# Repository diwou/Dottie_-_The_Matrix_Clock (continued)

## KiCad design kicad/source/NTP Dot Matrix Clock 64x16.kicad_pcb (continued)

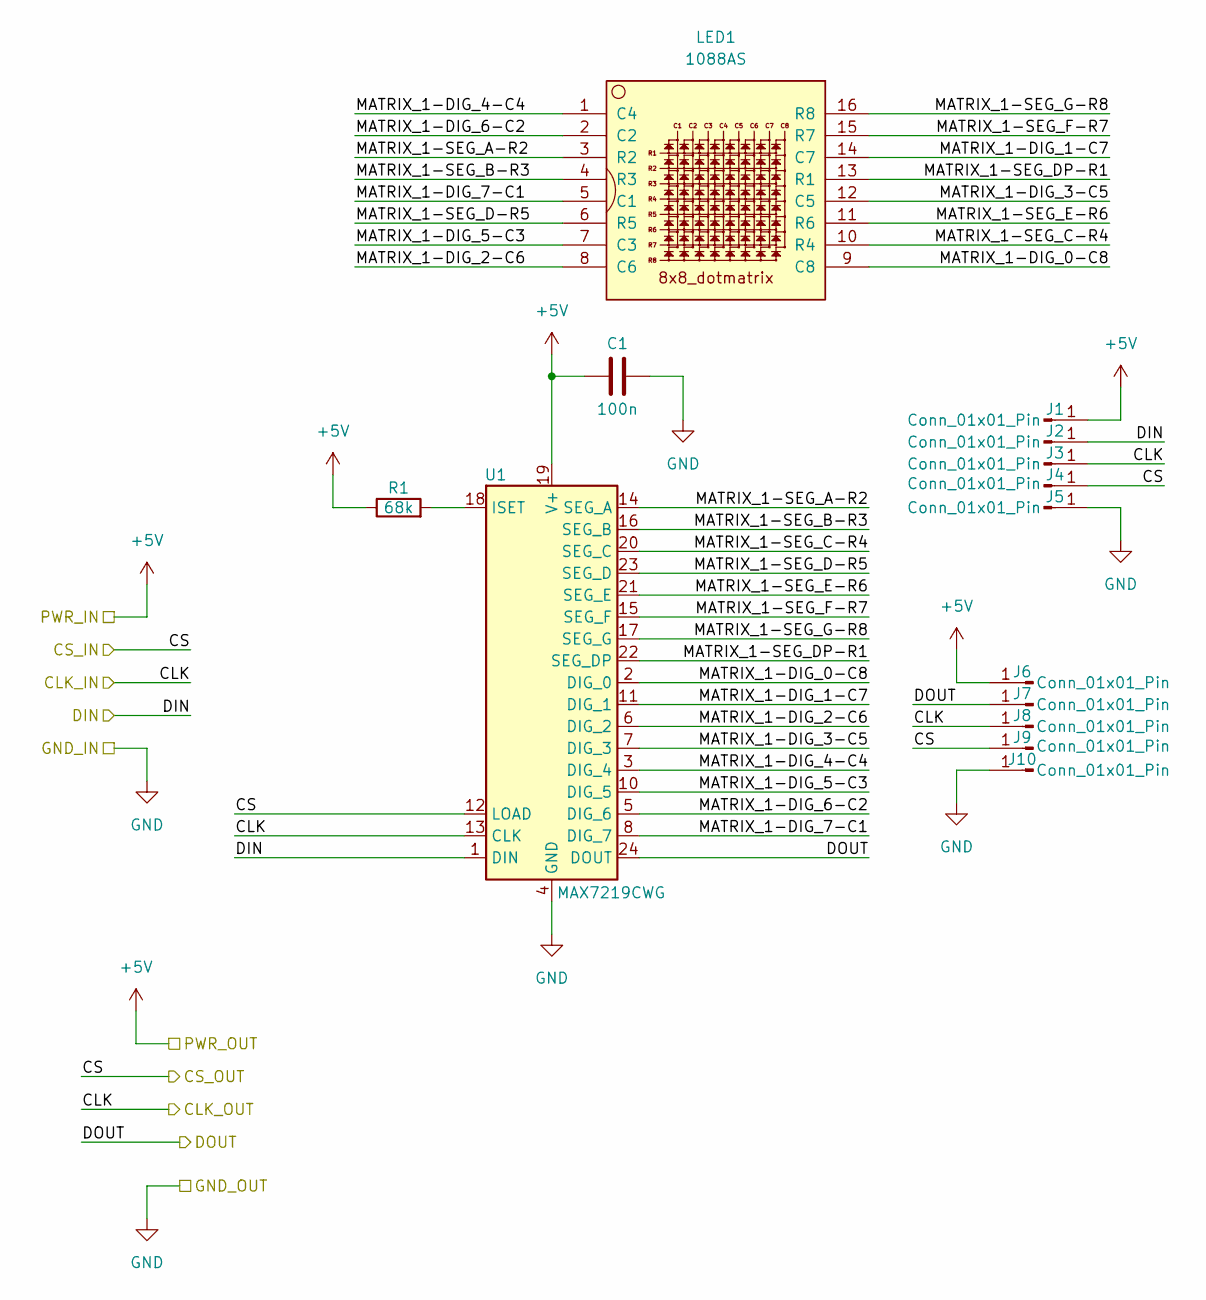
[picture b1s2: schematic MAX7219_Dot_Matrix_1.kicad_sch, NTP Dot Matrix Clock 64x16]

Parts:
C1: 100n; C_0805_2012Metric_Pad1.18x1.45mm_HandSolder
J1, J2, J3, J4, J5, J6, J7, J8, J9, J10: Conn_01x01_Pin; TestPoint_Pad_1.5x1.5mm
LED1: 1088AS; LED_1088_Pin_Header
R1: 68k; R_0805_2012Metric_Pad1.20x1.40mm_HandSolder
U1: MAX7219CWG; SOIC-24W_7.5x15.4mm_P1.27mm

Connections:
+5V: C1.1, J1.1 (Pin_1_1), J6.1 (Pin_1_1), R1.1, U1.19 (V+); also elsewhere on the board
/MAX7219 Dot Matrix 1/DOUT: J7.1 (Pin_1_1), U1.24 (DOUT); also elsewhere on the board
/MAX7219 Dot Matrix 1/MATRIX_1-DIG_0-C8: LED1.9 (C8), U1.2 (DIG_0)
/MAX7219 Dot Matrix 1/MATRIX_1-DIG_1-C7: LED1.14 (C7), U1.11 (DIG_1)
/MAX7219 Dot Matrix 1/MATRIX_1-DIG_2-C6: LED1.8 (C6), U1.6 (DIG_2)
/MAX7219 Dot Matrix 1/MATRIX_1-DIG_3-C5: LED1.12 (C5), U1.7 (DIG_3)
/MAX7219 Dot Matrix 1/MATRIX_1-DIG_4-C4: LED1.1 (C4), U1.3 (DIG_4)
/MAX7219 Dot Matrix 1/MATRIX_1-DIG_5-C3: LED1.7 (C3), U1.10 (DIG_5)
/MAX7219 Dot Matrix 1/MATRIX_1-DIG_6-C2: LED1.2 (C2), U1.5 (DIG_6)
/MAX7219 Dot Matrix 1/MATRIX_1-DIG_7-C1: LED1.5 (C1), U1.8 (DIG_7)
/MAX7219 Dot Matrix 1/MATRIX_1-SEG_A-R2: LED1.3 (R2), U1.14 (SEG_A)
/MAX7219 Dot Matrix 1/MATRIX_1-SEG_B-R3: LED1.4 (R3), U1.16 (SEG_B)
/MAX7219 Dot Matrix 1/MATRIX_1-SEG_C-R4: LED1.10 (R4), U1.20 (SEG_C)
/MAX7219 Dot Matrix 1/MATRIX_1-SEG_D-R5: LED1.6 (R5), U1.23 (SEG_D)
/MAX7219 Dot Matrix 1/MATRIX_1-SEG_DP-R1: LED1.13 (R1), U1.22 (SEG_DP)
/MAX7219 Dot Matrix 1/MATRIX_1-SEG_E-R6: LED1.11 (R6), U1.21 (SEG_E)
/MAX7219 Dot Matrix 1/MATRIX_1-SEG_F-R7: LED1.15 (R7), U1.15 (SEG_F)
/MAX7219 Dot Matrix 1/MATRIX_1-SEG_G-R8: LED1.16 (R8), U1.17 (SEG_G)
CLK: J3.1 (Pin_1_1), J8.1 (Pin_1_1), U1.13 (CLK); also elsewhere on the board
CS: J4.1 (Pin_1_1), J9.1 (Pin_1_1), U1.12 (LOAD); also elsewhere on the board
DIN: J2.1 (Pin_1_1), U1.1 (DIN); also elsewhere on the board
GND: C1.2, J5.1 (Pin_1_1), J10.1 (Pin_1_1), U1.4 (GND), U1.9 (GND); also elsewhere on the board
unnamed: R1.2, U1.18 (ISET)

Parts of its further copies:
C2, C3, C4, C5, C6, C7, C8, C9, C10, C11, C12, C13, C14, C15, C16: 100n; C_0805_2012Metric_Pad1.18x1.45mm_HandSolder
J11, J12, J13, J14, J15, J16, J17, J18, J19, J20, J21, J22, J23, J24, J25, J26, J27, J28, J29, J30, J31, J32, J33, J34, J35, J36, J37, J38, J39, J40, J41, J42, J43, J44, J45, J46, J47, J48, J49, J50, J51, J52, J53, J54, J55, J56, J57, J58, J59, J60, J61, J62, J63, J64, J65, J66, J67, J68, J69, J70, J71, J72, J73, J74, J75, J76, J77, J78, J79, J80, J83, J84, J85, J86, J87, J88, J89, J90, J91, J92, J93, J94, J95, J96, J97, J98, J99, J100, J101, J102, J103, J104, J105, J106, J107, J108, J109, J110, J111, J112, J113, J114, J115, J116, J117, J118, J119, J120, J121, J122, J123, J124, J125, J126, J127, J128, J129, J130, J131, J132, J133, J134, J135, J136, J137, J138, J139, J140, J141, J142, J143, J144, J145, J146, J147, J148, J149, J150, J151, J152, J153, J154, J155, J156, J157, J158, J159, J160, J161, J162: Conn_01x01_Pin; TestPoint_Pad_1.5x1.5mm
LED2, LED3, LED4, LED5, LED6, LED7, LED8, LED9, LED10, LED11, LED12, LED13, LED14, LED15, LED16: 1088AS; LED_1088_Pin_Header
R2, R3, R4, R5, R6, R7, R8, R9, R10, R11, R12, R13, R14, R15, R16: 68k; R_0805_2012Metric_Pad1.20x1.40mm_HandSolder
U2, U3, U4, U5, U6, U7, U8, U9, U10, U11, U12, U13, U14, U15, U16: MAX7219CWG; SOIC-24W_7.5x15.4mm_P1.27mm

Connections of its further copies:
+5V: C2.1, C3.1, C4.1, C5.1, C6.1, C7.1, C8.1, C9.1, C10.1, C11.1, C12.1, C13.1, C14.1, C15.1, C16.1, J11.1 (Pin_1_1), J16.1 (Pin_1_1), J21.1 (Pin_1_1), J26.1 (Pin_1_1), J31.1 (Pin_1_1), J36.1 (Pin_1_1), J41.1 (Pin_1_1), J46.1 (Pin_1_1), J51.1 (Pin_1_1), J56.1 (Pin_1_1), J61.1 (Pin_1_1), J66.1 (Pin_1_1), J71.1 (Pin_1_1), J76.1 (Pin_1_1), J83.1 (Pin_1_1), J88.1 (Pin_1_1), J93.1 (Pin_1_1), J98.1 (Pin_1_1), J103.1 (Pin_1_1), J108.1 (Pin_1_1), J113.1 (Pin_1_1), J118.1 (Pin_1_1), J123.1 (Pin_1_1), J128.1 (Pin_1_1), J133.1 (Pin_1_1), J138.1 (Pin_1_1), J143.1 (Pin_1_1), J148.1 (Pin_1_1), J153.1 (Pin_1_1), J158.1 (Pin_1_1), R2.1, R3.1, R4.1, R5.1, R6.1, R7.1, R8.1, R9.1, R10.1, R11.1, R12.1, R13.1, R14.1, R15.1, R16.1, U2.19 (V+), U3.19 (V+), U4.19 (V+), U5.19 (V+), U6.19 (V+), U7.19 (V+), U8.19 (V+), U9.19 (V+), U10.19 (V+), U11.19 (V+), U12.19 (V+), U13.19 (V+), U14.19 (V+), U15.19 (V+), U16.19 (V+); also elsewhere on the board
/MAX7219 Dot Matrix 1/DOUT: J12.1 (Pin_1_1), U2.1 (DIN); also elsewhere on the board
/MAX7219 Dot Matrix 2/DOUT: J17.1 (Pin_1_1), J22.1 (Pin_1_1), U2.24 (DOUT), U3.1 (DIN)
/MAX7219 Dot Matrix 2/MATRIX_1-DIG_0-C8: LED2.9 (C8), U2.2 (DIG_0)
/MAX7219 Dot Matrix 2/MATRIX_1-DIG_1-C7: LED2.14 (C7), U2.11 (DIG_1)
/MAX7219 Dot Matrix 2/MATRIX_1-DIG_2-C6: LED2.8 (C6), U2.6 (DIG_2)
/MAX7219 Dot Matrix 2/MATRIX_1-DIG_3-C5: LED2.12 (C5), U2.7 (DIG_3)
/MAX7219 Dot Matrix 2/MATRIX_1-DIG_4-C4: LED2.1 (C4), U2.3 (DIG_4)
/MAX7219 Dot Matrix 2/MATRIX_1-DIG_5-C3: LED2.7 (C3), U2.10 (DIG_5)
/MAX7219 Dot Matrix 2/MATRIX_1-DIG_6-C2: LED2.2 (C2), U2.5 (DIG_6)
/MAX7219 Dot Matrix 2/MATRIX_1-DIG_7-C1: LED2.5 (C1), U2.8 (DIG_7)
/MAX7219 Dot Matrix 2/MATRIX_1-SEG_A-R2: LED2.3 (R2), U2.14 (SEG_A)
/MAX7219 Dot Matrix 2/MATRIX_1-SEG_B-R3: LED2.4 (R3), U2.16 (SEG_B)
/MAX7219 Dot Matrix 2/MATRIX_1-SEG_C-R4: LED2.10 (R4), U2.20 (SEG_C)
/MAX7219 Dot Matrix 2/MATRIX_1-SEG_D-R5: LED2.6 (R5), U2.23 (SEG_D)
/MAX7219 Dot Matrix 2/MATRIX_1-SEG_DP-R1: LED2.13 (R1), U2.22 (SEG_DP)
/MAX7219 Dot Matrix 2/MATRIX_1-SEG_E-R6: LED2.11 (R6), U2.21 (SEG_E)
/MAX7219 Dot Matrix 2/MATRIX_1-SEG_F-R7: LED2.15 (R7), U2.15 (SEG_F)
/MAX7219 Dot Matrix 2/MATRIX_1-SEG_G-R8: LED2.16 (R8), U2.17 (SEG_G)
/MAX7219 Dot Matrix 3/DOUT: J27.1 (Pin_1_1), J32.1 (Pin_1_1), U3.24 (DOUT), U4.1 (DIN)
/MAX7219 Dot Matrix 3/MATRIX_1-DIG_0-C8: LED3.9 (C8), U3.2 (DIG_0)
/MAX7219 Dot Matrix 3/MATRIX_1-DIG_1-C7: LED3.14 (C7), U3.11 (DIG_1)
/MAX7219 Dot Matrix 3/MATRIX_1-DIG_2-C6: LED3.8 (C6), U3.6 (DIG_2)
/MAX7219 Dot Matrix 3/MATRIX_1-DIG_3-C5: LED3.12 (C5), U3.7 (DIG_3)
/MAX7219 Dot Matrix 3/MATRIX_1-DIG_4-C4: LED3.1 (C4), U3.3 (DIG_4)
/MAX7219 Dot Matrix 3/MATRIX_1-DIG_5-C3: LED3.7 (C3), U3.10 (DIG_5)
/MAX7219 Dot Matrix 3/MATRIX_1-DIG_6-C2: LED3.2 (C2), U3.5 (DIG_6)
/MAX7219 Dot Matrix 3/MATRIX_1-DIG_7-C1: LED3.5 (C1), U3.8 (DIG_7)
/MAX7219 Dot Matrix 3/MATRIX_1-SEG_A-R2: LED3.3 (R2), U3.14 (SEG_A)
/MAX7219 Dot Matrix 3/MATRIX_1-SEG_B-R3: LED3.4 (R3), U3.16 (SEG_B)
/MAX7219 Dot Matrix 3/MATRIX_1-SEG_C-R4: LED3.10 (R4), U3.20 (SEG_C)
/MAX7219 Dot Matrix 3/MATRIX_1-SEG_D-R5: LED3.6 (R5), U3.23 (SEG_D)
/MAX7219 Dot Matrix 3/MATRIX_1-SEG_DP-R1: LED3.13 (R1), U3.22 (SEG_DP)
/MAX7219 Dot Matrix 3/MATRIX_1-SEG_E-R6: LED3.11 (R6), U3.21 (SEG_E)
/MAX7219 Dot Matrix 3/MATRIX_1-SEG_F-R7: LED3.15 (R7), U3.15 (SEG_F)
/MAX7219 Dot Matrix 3/MATRIX_1-SEG_G-R8: LED3.16 (R8), U3.17 (SEG_G)
/MAX7219 Dot Matrix 4/DOUT: J37.1 (Pin_1_1), J42.1 (Pin_1_1), U4.24 (DOUT), U5.1 (DIN)
/MAX7219 Dot Matrix 4/MATRIX_1-DIG_0-C8: LED4.9 (C8), U4.2 (DIG_0)
/MAX7219 Dot Matrix 4/MATRIX_1-DIG_1-C7: LED4.14 (C7), U4.11 (DIG_1)
/MAX7219 Dot Matrix 4/MATRIX_1-DIG_2-C6: LED4.8 (C6), U4.6 (DIG_2)
/MAX7219 Dot Matrix 4/MATRIX_1-DIG_3-C5: LED4.12 (C5), U4.7 (DIG_3)
/MAX7219 Dot Matrix 4/MATRIX_1-DIG_4-C4: LED4.1 (C4), U4.3 (DIG_4)
/MAX7219 Dot Matrix 4/MATRIX_1-DIG_5-C3: LED4.7 (C3), U4.10 (DIG_5)
/MAX7219 Dot Matrix 4/MATRIX_1-DIG_6-C2: LED4.2 (C2), U4.5 (DIG_6)
/MAX7219 Dot Matrix 4/MATRIX_1-DIG_7-C1: LED4.5 (C1), U4.8 (DIG_7)
/MAX7219 Dot Matrix 4/MATRIX_1-SEG_A-R2: LED4.3 (R2), U4.14 (SEG_A)
/MAX7219 Dot Matrix 4/MATRIX_1-SEG_B-R3: LED4.4 (R3), U4.16 (SEG_B)
/MAX7219 Dot Matrix 4/MATRIX_1-SEG_C-R4: LED4.10 (R4), U4.20 (SEG_C)
/MAX7219 Dot Matrix 4/MATRIX_1-SEG_D-R5: LED4.6 (R5), U4.23 (SEG_D)
/MAX7219 Dot Matrix 4/MATRIX_1-SEG_DP-R1: LED4.13 (R1), U4.22 (SEG_DP)
/MAX7219 Dot Matrix 4/MATRIX_1-SEG_E-R6: LED4.11 (R6), U4.21 (SEG_E)
/MAX7219 Dot Matrix 4/MATRIX_1-SEG_F-R7: LED4.15 (R7), U4.15 (SEG_F)
/MAX7219 Dot Matrix 4/MATRIX_1-SEG_G-R8: LED4.16 (R8), U4.17 (SEG_G)
/MAX7219 Dot Matrix 5/DOUT: J47.1 (Pin_1_1), J52.1 (Pin_1_1), U5.24 (DOUT), U6.1 (DIN)
/MAX7219 Dot Matrix 5/MATRIX_1-DIG_0-C8: LED5.9 (C8), U5.2 (DIG_0)
/MAX7219 Dot Matrix 5/MATRIX_1-DIG_1-C7: LED5.14 (C7), U5.11 (DIG_1)
/MAX7219 Dot Matrix 5/MATRIX_1-DIG_2-C6: LED5.8 (C6), U5.6 (DIG_2)
/MAX7219 Dot Matrix 5/MATRIX_1-DIG_3-C5: LED5.12 (C5), U5.7 (DIG_3)
/MAX7219 Dot Matrix 5/MATRIX_1-DIG_4-C4: LED5.1 (C4), U5.3 (DIG_4)
/MAX7219 Dot Matrix 5/MATRIX_1-DIG_5-C3: LED5.7 (C3), U5.10 (DIG_5)
/MAX7219 Dot Matrix 5/MATRIX_1-DIG_6-C2: LED5.2 (C2), U5.5 (DIG_6)
/MAX7219 Dot Matrix 5/MATRIX_1-DIG_7-C1: LED5.5 (C1), U5.8 (DIG_7)
/MAX7219 Dot Matrix 5/MATRIX_1-SEG_A-R2: LED5.3 (R2), U5.14 (SEG_A)
/MAX7219 Dot Matrix 5/MATRIX_1-SEG_B-R3: LED5.4 (R3), U5.16 (SEG_B)
/MAX7219 Dot Matrix 5/MATRIX_1-SEG_C-R4: LED5.10 (R4), U5.20 (SEG_C)
/MAX7219 Dot Matrix 5/MATRIX_1-SEG_D-R5: LED5.6 (R5), U5.23 (SEG_D)
/MAX7219 Dot Matrix 5/MATRIX_1-SEG_DP-R1: LED5.13 (R1), U5.22 (SEG_DP)
/MAX7219 Dot Matrix 5/MATRIX_1-SEG_E-R6: LED5.11 (R6), U5.21 (SEG_E)
/MAX7219 Dot Matrix 5/MATRIX_1-SEG_F-R7: LED5.15 (R7), U5.15 (SEG_F)
/MAX7219 Dot Matrix 5/MATRIX_1-SEG_G-R8: LED5.16 (R8), U5.17 (SEG_G)
/MAX7219 Dot Matrix 6/DOUT: J57.1 (Pin_1_1), J62.1 (Pin_1_1), U6.24 (DOUT), U7.1 (DIN)
/MAX7219 Dot Matrix 6/MATRIX_1-DIG_0-C8: LED6.9 (C8), U6.2 (DIG_0)
/MAX7219 Dot Matrix 6/MATRIX_1-DIG_1-C7: LED6.14 (C7), U6.11 (DIG_1)
/MAX7219 Dot Matrix 6/MATRIX_1-DIG_2-C6: LED6.8 (C6), U6.6 (DIG_2)
/MAX7219 Dot Matrix 6/MATRIX_1-DIG_3-C5: LED6.12 (C5), U6.7 (DIG_3)
/MAX7219 Dot Matrix 6/MATRIX_1-DIG_4-C4: LED6.1 (C4), U6.3 (DIG_4)
/MAX7219 Dot Matrix 6/MATRIX_1-DIG_5-C3: LED6.7 (C3), U6.10 (DIG_5)
/MAX7219 Dot Matrix 6/MATRIX_1-DIG_6-C2: LED6.2 (C2), U6.5 (DIG_6)
/MAX7219 Dot Matrix 6/MATRIX_1-DIG_7-C1: LED6.5 (C1), U6.8 (DIG_7)
/MAX7219 Dot Matrix 6/MATRIX_1-SEG_A-R2: LED6.3 (R2), U6.14 (SEG_A)
/MAX7219 Dot Matrix 6/MATRIX_1-SEG_B-R3: LED6.4 (R3), U6.16 (SEG_B)
/MAX7219 Dot Matrix 6/MATRIX_1-SEG_C-R4: LED6.10 (R4), U6.20 (SEG_C)
/MAX7219 Dot Matrix 6/MATRIX_1-SEG_D-R5: LED6.6 (R5), U6.23 (SEG_D)
/MAX7219 Dot Matrix 6/MATRIX_1-SEG_DP-R1: LED6.13 (R1), U6.22 (SEG_DP)
/MAX7219 Dot Matrix 6/MATRIX_1-SEG_E-R6: LED6.11 (R6), U6.21 (SEG_E)
/MAX7219 Dot Matrix 6/MATRIX_1-SEG_F-R7: LED6.15 (R7), U6.15 (SEG_F)
/MAX7219 Dot Matrix 6/MATRIX_1-SEG_G-R8: LED6.16 (R8), U6.17 (SEG_G)
/MAX7219 Dot Matrix 7/DOUT: J67.1 (Pin_1_1), J72.1 (Pin_1_1), U7.24 (DOUT), U8.1 (DIN)
/MAX7219 Dot Matrix 7/MATRIX_1-DIG_0-C8: LED7.9 (C8), U7.2 (DIG_0)
/MAX7219 Dot Matrix 7/MATRIX_1-DIG_1-C7: LED7.14 (C7), U7.11 (DIG_1)
/MAX7219 Dot Matrix 7/MATRIX_1-DIG_2-C6: LED7.8 (C6), U7.6 (DIG_2)
/MAX7219 Dot Matrix 7/MATRIX_1-DIG_3-C5: LED7.12 (C5), U7.7 (DIG_3)
/MAX7219 Dot Matrix 7/MATRIX_1-DIG_4-C4: LED7.1 (C4), U7.3 (DIG_4)
/MAX7219 Dot Matrix 7/MATRIX_1-DIG_5-C3: LED7.7 (C3), U7.10 (DIG_5)
/MAX7219 Dot Matrix 7/MATRIX_1-DIG_6-C2: LED7.2 (C2), U7.5 (DIG_6)
/MAX7219 Dot Matrix 7/MATRIX_1-DIG_7-C1: LED7.5 (C1), U7.8 (DIG_7)
/MAX7219 Dot Matrix 7/MATRIX_1-SEG_A-R2: LED7.3 (R2), U7.14 (SEG_A)
/MAX7219 Dot Matrix 7/MATRIX_1-SEG_B-R3: LED7.4 (R3), U7.16 (SEG_B)
/MAX7219 Dot Matrix 7/MATRIX_1-SEG_C-R4: LED7.10 (R4), U7.20 (SEG_C)
/MAX7219 Dot Matrix 7/MATRIX_1-SEG_D-R5: LED7.6 (R5), U7.23 (SEG_D)
/MAX7219 Dot Matrix 7/MATRIX_1-SEG_DP-R1: LED7.13 (R1), U7.22 (SEG_DP)
/MAX7219 Dot Matrix 7/MATRIX_1-SEG_E-R6: LED7.11 (R6), U7.21 (SEG_E)
/MAX7219 Dot Matrix 7/MATRIX_1-SEG_F-R7: LED7.15 (R7), U7.15 (SEG_F)
/MAX7219 Dot Matrix 7/MATRIX_1-SEG_G-R8: LED7.16 (R8), U7.17 (SEG_G)
/MAX7219 Dot Matrix 8/DOUT: J77.1 (Pin_1_1), J84.1 (Pin_1_1), U8.24 (DOUT), U9.1 (DIN)
/MAX7219 Dot Matrix 8/MATRIX_1-DIG_0-C8: LED8.9 (C8), U8.2 (DIG_0)
/MAX7219 Dot Matrix 8/MATRIX_1-DIG_1-C7: LED8.14 (C7), U8.11 (DIG_1)
/MAX7219 Dot Matrix 8/MATRIX_1-DIG_2-C6: LED8.8 (C6), U8.6 (DIG_2)
/MAX7219 Dot Matrix 8/MATRIX_1-DIG_3-C5: LED8.12 (C5), U8.7 (DIG_3)
/MAX7219 Dot Matrix 8/MATRIX_1-DIG_4-C4: LED8.1 (C4), U8.3 (DIG_4)
/MAX7219 Dot Matrix 8/MATRIX_1-DIG_5-C3: LED8.7 (C3), U8.10 (DIG_5)
/MAX7219 Dot Matrix 8/MATRIX_1-DIG_6-C2: LED8.2 (C2), U8.5 (DIG_6)
/MAX7219 Dot Matrix 8/MATRIX_1-DIG_7-C1: LED8.5 (C1), U8.8 (DIG_7)
/MAX7219 Dot Matrix 8/MATRIX_1-SEG_A-R2: LED8.3 (R2), U8.14 (SEG_A)
/MAX7219 Dot Matrix 8/MATRIX_1-SEG_B-R3: LED8.4 (R3), U8.16 (SEG_B)
/MAX7219 Dot Matrix 8/MATRIX_1-SEG_C-R4: LED8.10 (R4), U8.20 (SEG_C)
/MAX7219 Dot Matrix 8/MATRIX_1-SEG_D-R5: LED8.6 (R5), U8.23 (SEG_D)
/MAX7219 Dot Matrix 8/MATRIX_1-SEG_DP-R1: LED8.13 (R1), U8.22 (SEG_DP)
/MAX7219 Dot Matrix 8/MATRIX_1-SEG_E-R6: LED8.11 (R6), U8.21 (SEG_E)
/MAX7219 Dot Matrix 8/MATRIX_1-SEG_F-R7: LED8.15 (R7), U8.15 (SEG_F)
/MAX7219 Dot Matrix 8/MATRIX_1-SEG_G-R8: LED8.16 (R8), U8.17 (SEG_G)
/MAX7219 Dot Matrix 9/MATRIX_1-DIG_0-C8: LED9.9 (C8), U9.2 (DIG_0)
/MAX7219 Dot Matrix 9/MATRIX_1-DIG_1-C7: LED9.14 (C7), U9.11 (DIG_1)
/MAX7219 Dot Matrix 9/MATRIX_1-DIG_2-C6: LED9.8 (C6), U9.6 (DIG_2)
/MAX7219 Dot Matrix 9/MATRIX_1-DIG_3-C5: LED9.12 (C5), U9.7 (DIG_3)
/MAX7219 Dot Matrix 9/MATRIX_1-DIG_4-C4: LED9.1 (C4), U9.3 (DIG_4)
/MAX7219 Dot Matrix 9/MATRIX_1-DIG_5-C3: LED9.7 (C3), U9.10 (DIG_5)
/MAX7219 Dot Matrix 9/MATRIX_1-DIG_6-C2: LED9.2 (C2), U9.5 (DIG_6)
/MAX7219 Dot Matrix 9/MATRIX_1-DIG_7-C1: LED9.5 (C1), U9.8 (DIG_7)
/MAX7219 Dot Matrix 9/MATRIX_1-SEG_A-R2: LED9.3 (R2), U9.14 (SEG_A)
/MAX7219 Dot Matrix 9/MATRIX_1-SEG_B-R3: LED9.4 (R3), U9.16 (SEG_B)
/MAX7219 Dot Matrix 9/MATRIX_1-SEG_C-R4: LED9.10 (R4), U9.20 (SEG_C)
/MAX7219 Dot Matrix 9/MATRIX_1-SEG_D-R5: LED9.6 (R5), U9.23 (SEG_D)
/MAX7219 Dot Matrix 9/MATRIX_1-SEG_DP-R1: LED9.13 (R1), U9.22 (SEG_DP)
/MAX7219 Dot Matrix 9/MATRIX_1-SEG_E-R6: LED9.11 (R6), U9.21 (SEG_E)
/MAX7219 Dot Matrix 9/MATRIX_1-SEG_F-R7: LED9.15 (R7), U9.15 (SEG_F)
/MAX7219 Dot Matrix 9/MATRIX_1-SEG_G-R8: LED9.16 (R8), U9.17 (SEG_G)
/MAX7219 Dot Matrix 10/DIN: J89.1 (Pin_1_1), J94.1 (Pin_1_1), U9.24 (DOUT), U10.1 (DIN)
/MAX7219 Dot Matrix 10/DOUT: J99.1 (Pin_1_1), J104.1 (Pin_1_1), U10.24 (DOUT), U11.1 (DIN)
/MAX7219 Dot Matrix 10/MATRIX_1-DIG_0-C8: LED10.9 (C8), U10.2 (DIG_0)
/MAX7219 Dot Matrix 10/MATRIX_1-DIG_1-C7: LED10.14 (C7), U10.11 (DIG_1)
/MAX7219 Dot Matrix 10/MATRIX_1-DIG_2-C6: LED10.8 (C6), U10.6 (DIG_2)
/MAX7219 Dot Matrix 10/MATRIX_1-DIG_3-C5: LED10.12 (C5), U10.7 (DIG_3)
/MAX7219 Dot Matrix 10/MATRIX_1-DIG_4-C4: LED10.1 (C4), U10.3 (DIG_4)
/MAX7219 Dot Matrix 10/MATRIX_1-DIG_5-C3: LED10.7 (C3), U10.10 (DIG_5)
/MAX7219 Dot Matrix 10/MATRIX_1-DIG_6-C2: LED10.2 (C2), U10.5 (DIG_6)
/MAX7219 Dot Matrix 10/MATRIX_1-DIG_7-C1: LED10.5 (C1), U10.8 (DIG_7)
/MAX7219 Dot Matrix 10/MATRIX_1-SEG_A-R2: LED10.3 (R2), U10.14 (SEG_A)
/MAX7219 Dot Matrix 10/MATRIX_1-SEG_B-R3: LED10.4 (R3), U10.16 (SEG_B)
/MAX7219 Dot Matrix 10/MATRIX_1-SEG_C-R4: LED10.10 (R4), U10.20 (SEG_C)
/MAX7219 Dot Matrix 10/MATRIX_1-SEG_D-R5: LED10.6 (R5), U10.23 (SEG_D)
/MAX7219 Dot Matrix 10/MATRIX_1-SEG_DP-R1: LED10.13 (R1), U10.22 (SEG_DP)
/MAX7219 Dot Matrix 10/MATRIX_1-SEG_E-R6: LED10.11 (R6), U10.21 (SEG_E)
/MAX7219 Dot Matrix 10/MATRIX_1-SEG_F-R7: LED10.15 (R7), U10.15 (SEG_F)
/MAX7219 Dot Matrix 10/MATRIX_1-SEG_G-R8: LED10.16 (R8), U10.17 (SEG_G)
/MAX7219 Dot Matrix 11/DOUT: J109.1 (Pin_1_1), J114.1 (Pin_1_1), U11.24 (DOUT), U12.1 (DIN)
/MAX7219 Dot Matrix 11/MATRIX_1-DIG_0-C8: LED11.9 (C8), U11.2 (DIG_0)
/MAX7219 Dot Matrix 11/MATRIX_1-DIG_1-C7: LED11.14 (C7), U11.11 (DIG_1)
/MAX7219 Dot Matrix 11/MATRIX_1-DIG_2-C6: LED11.8 (C6), U11.6 (DIG_2)
/MAX7219 Dot Matrix 11/MATRIX_1-DIG_3-C5: LED11.12 (C5), U11.7 (DIG_3)
/MAX7219 Dot Matrix 11/MATRIX_1-DIG_4-C4: LED11.1 (C4), U11.3 (DIG_4)
/MAX7219 Dot Matrix 11/MATRIX_1-DIG_5-C3: LED11.7 (C3), U11.10 (DIG_5)
/MAX7219 Dot Matrix 11/MATRIX_1-DIG_6-C2: LED11.2 (C2), U11.5 (DIG_6)
/MAX7219 Dot Matrix 11/MATRIX_1-DIG_7-C1: LED11.5 (C1), U11.8 (DIG_7)
/MAX7219 Dot Matrix 11/MATRIX_1-SEG_A-R2: LED11.3 (R2), U11.14 (SEG_A)
/MAX7219 Dot Matrix 11/MATRIX_1-SEG_B-R3: LED11.4 (R3), U11.16 (SEG_B)
/MAX7219 Dot Matrix 11/MATRIX_1-SEG_C-R4: LED11.10 (R4), U11.20 (SEG_C)
/MAX7219 Dot Matrix 11/MATRIX_1-SEG_D-R5: LED11.6 (R5), U11.23 (SEG_D)
/MAX7219 Dot Matrix 11/MATRIX_1-SEG_DP-R1: LED11.13 (R1), U11.22 (SEG_DP)
/MAX7219 Dot Matrix 11/MATRIX_1-SEG_E-R6: LED11.11 (R6), U11.21 (SEG_E)
/MAX7219 Dot Matrix 11/MATRIX_1-SEG_F-R7: LED11.15 (R7), U11.15 (SEG_F)
/MAX7219 Dot Matrix 11/MATRIX_1-SEG_G-R8: LED11.16 (R8), U11.17 (SEG_G)
/MAX7219 Dot Matrix 12/DOUT: J119.1 (Pin_1_1), J124.1 (Pin_1_1), U12.24 (DOUT), U13.1 (DIN)
/MAX7219 Dot Matrix 12/MATRIX_1-DIG_0-C8: LED12.9 (C8), U12.2 (DIG_0)
/MAX7219 Dot Matrix 12/MATRIX_1-DIG_1-C7: LED12.14 (C7), U12.11 (DIG_1)
/MAX7219 Dot Matrix 12/MATRIX_1-DIG_2-C6: LED12.8 (C6), U12.6 (DIG_2)
/MAX7219 Dot Matrix 12/MATRIX_1-DIG_3-C5: LED12.12 (C5), U12.7 (DIG_3)
/MAX7219 Dot Matrix 12/MATRIX_1-DIG_4-C4: LED12.1 (C4), U12.3 (DIG_4)
/MAX7219 Dot Matrix 12/MATRIX_1-DIG_5-C3: LED12.7 (C3), U12.10 (DIG_5)
/MAX7219 Dot Matrix 12/MATRIX_1-DIG_6-C2: LED12.2 (C2), U12.5 (DIG_6)
/MAX7219 Dot Matrix 12/MATRIX_1-DIG_7-C1: LED12.5 (C1), U12.8 (DIG_7)
/MAX7219 Dot Matrix 12/MATRIX_1-SEG_A-R2: LED12.3 (R2), U12.14 (SEG_A)
/MAX7219 Dot Matrix 12/MATRIX_1-SEG_B-R3: LED12.4 (R3), U12.16 (SEG_B)
/MAX7219 Dot Matrix 12/MATRIX_1-SEG_C-R4: LED12.10 (R4), U12.20 (SEG_C)
/MAX7219 Dot Matrix 12/MATRIX_1-SEG_D-R5: LED12.6 (R5), U12.23 (SEG_D)
/MAX7219 Dot Matrix 12/MATRIX_1-SEG_DP-R1: LED12.13 (R1), U12.22 (SEG_DP)
/MAX7219 Dot Matrix 12/MATRIX_1-SEG_E-R6: LED12.11 (R6), U12.21 (SEG_E)
/MAX7219 Dot Matrix 12/MATRIX_1-SEG_F-R7: LED12.15 (R7), U12.15 (SEG_F)
/MAX7219 Dot Matrix 12/MATRIX_1-SEG_G-R8: LED12.16 (R8), U12.17 (SEG_G)
/MAX7219 Dot Matrix 13/DOUT: J129.1 (Pin_1_1), J134.1 (Pin_1_1), U13.24 (DOUT), U14.1 (DIN)
/MAX7219 Dot Matrix 13/MATRIX_1-DIG_0-C8: LED13.9 (C8), U13.2 (DIG_0)
/MAX7219 Dot Matrix 13/MATRIX_1-DIG_1-C7: LED13.14 (C7), U13.11 (DIG_1)
/MAX7219 Dot Matrix 13/MATRIX_1-DIG_2-C6: LED13.8 (C6), U13.6 (DIG_2)
/MAX7219 Dot Matrix 13/MATRIX_1-DIG_3-C5: LED13.12 (C5), U13.7 (DIG_3)
/MAX7219 Dot Matrix 13/MATRIX_1-DIG_4-C4: LED13.1 (C4), U13.3 (DIG_4)
/MAX7219 Dot Matrix 13/MATRIX_1-DIG_5-C3: LED13.7 (C3), U13.10 (DIG_5)
/MAX7219 Dot Matrix 13/MATRIX_1-DIG_6-C2: LED13.2 (C2), U13.5 (DIG_6)
/MAX7219 Dot Matrix 13/MATRIX_1-DIG_7-C1: LED13.5 (C1), U13.8 (DIG_7)
/MAX7219 Dot Matrix 13/MATRIX_1-SEG_A-R2: LED13.3 (R2), U13.14 (SEG_A)
/MAX7219 Dot Matrix 13/MATRIX_1-SEG_B-R3: LED13.4 (R3), U13.16 (SEG_B)
/MAX7219 Dot Matrix 13/MATRIX_1-SEG_C-R4: LED13.10 (R4), U13.20 (SEG_C)
/MAX7219 Dot Matrix 13/MATRIX_1-SEG_D-R5: LED13.6 (R5), U13.23 (SEG_D)
/MAX7219 Dot Matrix 13/MATRIX_1-SEG_DP-R1: LED13.13 (R1), U13.22 (SEG_DP)
/MAX7219 Dot Matrix 13/MATRIX_1-SEG_E-R6: LED13.11 (R6), U13.21 (SEG_E)
/MAX7219 Dot Matrix 13/MATRIX_1-SEG_F-R7: LED13.15 (R7), U13.15 (SEG_F)
/MAX7219 Dot Matrix 13/MATRIX_1-SEG_G-R8: LED13.16 (R8), U13.17 (SEG_G)
/MAX7219 Dot Matrix 14/DOUT: J139.1 (Pin_1_1), J144.1 (Pin_1_1), U14.24 (DOUT), U15.1 (DIN)
/MAX7219 Dot Matrix 14/MATRIX_1-DIG_0-C8: LED14.9 (C8), U14.2 (DIG_0)
/MAX7219 Dot Matrix 14/MATRIX_1-DIG_1-C7: LED14.14 (C7), U14.11 (DIG_1)
/MAX7219 Dot Matrix 14/MATRIX_1-DIG_2-C6: LED14.8 (C6), U14.6 (DIG_2)
/MAX7219 Dot Matrix 14/MATRIX_1-DIG_3-C5: LED14.12 (C5), U14.7 (DIG_3)
/MAX7219 Dot Matrix 14/MATRIX_1-DIG_4-C4: LED14.1 (C4), U14.3 (DIG_4)
/MAX7219 Dot Matrix 14/MATRIX_1-DIG_5-C3: LED14.7 (C3), U14.10 (DIG_5)
/MAX7219 Dot Matrix 14/MATRIX_1-DIG_6-C2: LED14.2 (C2), U14.5 (DIG_6)
/MAX7219 Dot Matrix 14/MATRIX_1-DIG_7-C1: LED14.5 (C1), U14.8 (DIG_7)
/MAX7219 Dot Matrix 14/MATRIX_1-SEG_A-R2: LED14.3 (R2), U14.14 (SEG_A)
/MAX7219 Dot Matrix 14/MATRIX_1-SEG_B-R3: LED14.4 (R3), U14.16 (SEG_B)
/MAX7219 Dot Matrix 14/MATRIX_1-SEG_C-R4: LED14.10 (R4), U14.20 (SEG_C)
/MAX7219 Dot Matrix 14/MATRIX_1-SEG_D-R5: LED14.6 (R5), U14.23 (SEG_D)
/MAX7219 Dot Matrix 14/MATRIX_1-SEG_DP-R1: LED14.13 (R1), U14.22 (SEG_DP)
/MAX7219 Dot Matrix 14/MATRIX_1-SEG_E-R6: LED14.11 (R6), U14.21 (SEG_E)
/MAX7219 Dot Matrix 14/MATRIX_1-SEG_F-R7: LED14.15 (R7), U14.15 (SEG_F)
/MAX7219 Dot Matrix 14/MATRIX_1-SEG_G-R8: LED14.16 (R8), U14.17 (SEG_G)
/MAX7219 Dot Matrix 15/DOUT: J149.1 (Pin_1_1), J154.1 (Pin_1_1), U15.24 (DOUT), U16.1 (DIN)
/MAX7219 Dot Matrix 15/MATRIX_1-DIG_0-C8: LED15.9 (C8), U15.2 (DIG_0)
/MAX7219 Dot Matrix 15/MATRIX_1-DIG_1-C7: LED15.14 (C7), U15.11 (DIG_1)
/MAX7219 Dot Matrix 15/MATRIX_1-DIG_2-C6: LED15.8 (C6), U15.6 (DIG_2)
/MAX7219 Dot Matrix 15/MATRIX_1-DIG_3-C5: LED15.12 (C5), U15.7 (DIG_3)
/MAX7219 Dot Matrix 15/MATRIX_1-DIG_4-C4: LED15.1 (C4), U15.3 (DIG_4)
/MAX7219 Dot Matrix 15/MATRIX_1-DIG_5-C3: LED15.7 (C3), U15.10 (DIG_5)
/MAX7219 Dot Matrix 15/MATRIX_1-DIG_6-C2: LED15.2 (C2), U15.5 (DIG_6)
/MAX7219 Dot Matrix 15/MATRIX_1-DIG_7-C1: LED15.5 (C1), U15.8 (DIG_7)
/MAX7219 Dot Matrix 15/MATRIX_1-SEG_A-R2: LED15.3 (R2), U15.14 (SEG_A)
/MAX7219 Dot Matrix 15/MATRIX_1-SEG_B-R3: LED15.4 (R3), U15.16 (SEG_B)
/MAX7219 Dot Matrix 15/MATRIX_1-SEG_C-R4: LED15.10 (R4), U15.20 (SEG_C)
/MAX7219 Dot Matrix 15/MATRIX_1-SEG_D-R5: LED15.6 (R5), U15.23 (SEG_D)
/MAX7219 Dot Matrix 15/MATRIX_1-SEG_DP-R1: LED15.13 (R1), U15.22 (SEG_DP)
/MAX7219 Dot Matrix 15/MATRIX_1-SEG_E-R6: LED15.11 (R6), U15.21 (SEG_E)
/MAX7219 Dot Matrix 15/MATRIX_1-SEG_F-R7: LED15.15 (R7), U15.15 (SEG_F)
/MAX7219 Dot Matrix 15/MATRIX_1-SEG_G-R8: LED15.16 (R8), U15.17 (SEG_G)
/MAX7219 Dot Matrix 16/MATRIX_1-DIG_0-C8: LED16.9 (C8), U16.2 (DIG_0)
/MAX7219 Dot Matrix 16/MATRIX_1-DIG_1-C7: LED16.14 (C7), U16.11 (DIG_1)
/MAX7219 Dot Matrix 16/MATRIX_1-DIG_2-C6: LED16.8 (C6), U16.6 (DIG_2)
/MAX7219 Dot Matrix 16/MATRIX_1-DIG_3-C5: LED16.12 (C5), U16.7 (DIG_3)
/MAX7219 Dot Matrix 16/MATRIX_1-DIG_4-C4: LED16.1 (C4), U16.3 (DIG_4)
/MAX7219 Dot Matrix 16/MATRIX_1-DIG_5-C3: LED16.7 (C3), U16.10 (DIG_5)
/MAX7219 Dot Matrix 16/MATRIX_1-DIG_6-C2: LED16.2 (C2), U16.5 (DIG_6)
/MAX7219 Dot Matrix 16/MATRIX_1-DIG_7-C1: LED16.5 (C1), U16.8 (DIG_7)
/MAX7219 Dot Matrix 16/MATRIX_1-SEG_A-R2: LED16.3 (R2), U16.14 (SEG_A)
/MAX7219 Dot Matrix 16/MATRIX_1-SEG_B-R3: LED16.4 (R3), U16.16 (SEG_B)
/MAX7219 Dot Matrix 16/MATRIX_1-SEG_C-R4: LED16.10 (R4), U16.20 (SEG_C)
/MAX7219 Dot Matrix 16/MATRIX_1-SEG_D-R5: LED16.6 (R5), U16.23 (SEG_D)
/MAX7219 Dot Matrix 16/MATRIX_1-SEG_DP-R1: LED16.13 (R1), U16.22 (SEG_DP)
/MAX7219 Dot Matrix 16/MATRIX_1-SEG_E-R6: LED16.11 (R6), U16.21 (SEG_E)
/MAX7219 Dot Matrix 16/MATRIX_1-SEG_F-R7: LED16.15 (R7), U16.15 (SEG_F)
/MAX7219 Dot Matrix 16/MATRIX_1-SEG_G-R8: LED16.16 (R8), U16.17 (SEG_G)
CLK: J13.1 (Pin_1_1), J18.1 (Pin_1_1), J23.1 (Pin_1_1), J28.1 (Pin_1_1), J33.1 (Pin_1_1), J38.1 (Pin_1_1), J43.1 (Pin_1_1), J48.1 (Pin_1_1), J53.1 (Pin_1_1), J58.1 (Pin_1_1), J63.1 (Pin_1_1), J68.1 (Pin_1_1), J73.1 (Pin_1_1), J78.1 (Pin_1_1), J85.1 (Pin_1_1), J90.1 (Pin_1_1), J95.1 (Pin_1_1), J100.1 (Pin_1_1), J105.1 (Pin_1_1), J110.1 (Pin_1_1), J115.1 (Pin_1_1), J120.1 (Pin_1_1), J125.1 (Pin_1_1), J130.1 (Pin_1_1), J135.1 (Pin_1_1), J140.1 (Pin_1_1), J145.1 (Pin_1_1), J150.1 (Pin_1_1), J155.1 (Pin_1_1), J160.1 (Pin_1_1), U2.13 (CLK), U3.13 (CLK), U4.13 (CLK), U5.13 (CLK), U6.13 (CLK), U7.13 (CLK), U8.13 (CLK), U9.13 (CLK), U10.13 (CLK), U11.13 (CLK), U12.13 (CLK), U13.13 (CLK), U14.13 (CLK), U15.13 (CLK), U16.13 (CLK); also elsewhere on the board
CS: J14.1 (Pin_1_1), J19.1 (Pin_1_1), J24.1 (Pin_1_1), J29.1 (Pin_1_1), J34.1 (Pin_1_1), J39.1 (Pin_1_1), J44.1 (Pin_1_1), J49.1 (Pin_1_1), J54.1 (Pin_1_1), J59.1 (Pin_1_1), J64.1 (Pin_1_1), J69.1 (Pin_1_1), J74.1 (Pin_1_1), J79.1 (Pin_1_1), J86.1 (Pin_1_1), J91.1 (Pin_1_1), J96.1 (Pin_1_1), J101.1 (Pin_1_1), J106.1 (Pin_1_1), J111.1 (Pin_1_1), J116.1 (Pin_1_1), J121.1 (Pin_1_1), J126.1 (Pin_1_1), J131.1 (Pin_1_1), J136.1 (Pin_1_1), J141.1 (Pin_1_1), J146.1 (Pin_1_1), J151.1 (Pin_1_1), J156.1 (Pin_1_1), J161.1 (Pin_1_1), U2.12 (LOAD), U3.12 (LOAD), U4.12 (LOAD), U5.12 (LOAD), U6.12 (LOAD), U7.12 (LOAD), U8.12 (LOAD), U9.12 (LOAD), U10.12 (LOAD), U11.12 (LOAD), U12.12 (LOAD), U13.12 (LOAD), U14.12 (LOAD), U15.12 (LOAD), U16.12 (LOAD); also elsewhere on the board
DOUT: J159.1 (Pin_1_1), U16.24 (DOUT); also elsewhere on the board
GND: C2.2, C3.2, C4.2, C5.2, C6.2, C7.2, C8.2, C9.2, C10.2, C11.2, C12.2, C13.2, C14.2, C15.2, C16.2, J15.1 (Pin_1_1), J20.1 (Pin_1_1), J25.1 (Pin_1_1), J30.1 (Pin_1_1), J35.1 (Pin_1_1), J40.1 (Pin_1_1), J45.1 (Pin_1_1), J50.1 (Pin_1_1), J55.1 (Pin_1_1), J60.1 (Pin_1_1), J65.1 (Pin_1_1), J70.1 (Pin_1_1), J75.1 (Pin_1_1), J80.1 (Pin_1_1), J87.1 (Pin_1_1), J92.1 (Pin_1_1), J97.1 (Pin_1_1), J102.1 (Pin_1_1), J107.1 (Pin_1_1), J112.1 (Pin_1_1), J117.1 (Pin_1_1), J122.1 (Pin_1_1), J127.1 (Pin_1_1), J132.1 (Pin_1_1), J137.1 (Pin_1_1), J142.1 (Pin_1_1), J147.1 (Pin_1_1), J152.1 (Pin_1_1), J157.1 (Pin_1_1), J162.1 (Pin_1_1), U2.4 (GND), U2.9 (GND), U3.4 (GND), U3.9 (GND), U4.4 (GND), U4.9 (GND), U5.4 (GND), U5.9 (GND), U6.4 (GND), U6.9 (GND), U7.4 (GND), U7.9 (GND), U8.4 (GND), U8.9 (GND), U9.4 (GND), U9.9 (GND), U10.4 (GND), U10.9 (GND), U11.4 (GND), U11.9 (GND), U12.4 (GND), U12.9 (GND), U13.4 (GND), U13.9 (GND), U14.4 (GND), U14.9 (GND), U15.4 (GND), U15.9 (GND), U16.4 (GND), U16.9 (GND); also elsewhere on the board
unnamed: R2.2, U2.18 (ISET)
unnamed: R3.2, U3.18 (ISET)
unnamed: R4.2, U4.18 (ISET)
unnamed: R5.2, U5.18 (ISET)
unnamed: R6.2, U6.18 (ISET)
unnamed: R7.2, U7.18 (ISET)
unnamed: R8.2, U8.18 (ISET)
unnamed: R9.2, U9.18 (ISET)
unnamed: R10.2, U10.18 (ISET)
unnamed: R11.2, U11.18 (ISET)
unnamed: R12.2, U12.18 (ISET)
unnamed: R13.2, U13.18 (ISET)
unnamed: R14.2, U14.18 (ISET)
unnamed: R15.2, U15.18 (ISET)
unnamed: R16.2, U16.18 (ISET)

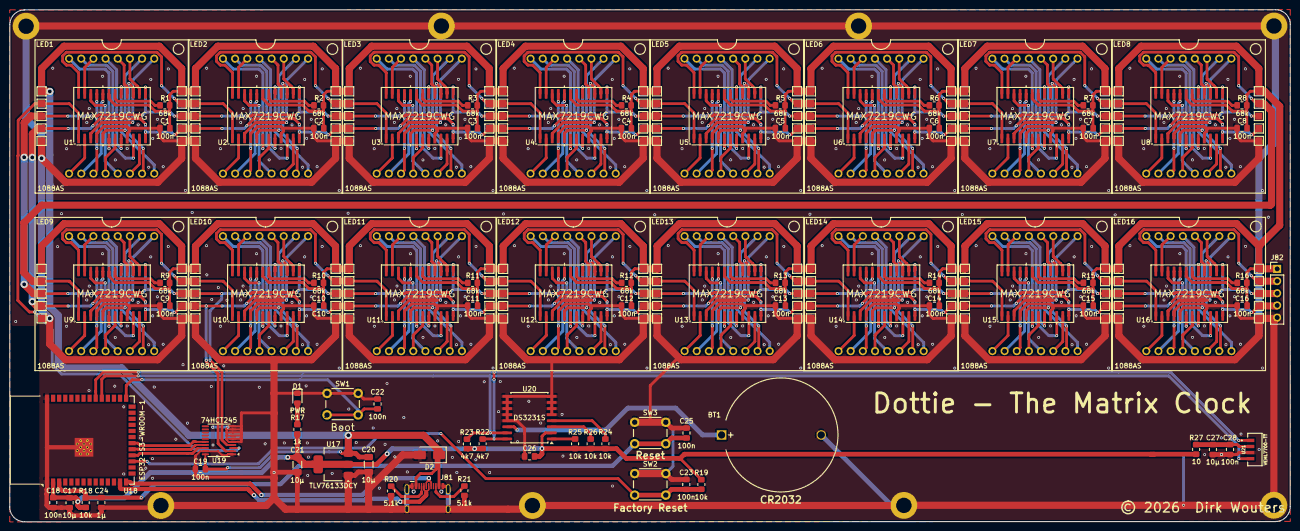
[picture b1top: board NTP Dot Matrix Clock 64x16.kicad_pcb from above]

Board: 2 copper layers, 267.4 x 106.9 mm, 268 parts (0 on the bottom side), 312 nets.

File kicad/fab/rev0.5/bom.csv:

Designator,Footprint,Quantity,Value,LCSC Part #
BT1,BatteryHolder_MYOUNG_BS-07-A1BJ001_CR2032,1,CR2032,
"C1, C10, C11, C12, C13, C14, C15, C16, C18, C19, C2, C22, C23, C25, C26, C28, C3, C4, C5, C6, C7, C8, C9",0805,23,100n,
"C17, C27",0805,2,10µ,
"C20, C21",1206,2,10µ,
C24,0805,1,1µ,
D1,0805,1,PWR,
D2,D_SMA,1,SS14,
"J1, J10, J100, J101, J102, J103, J104, J105, J106, J107, J108, J109, J11, J110, J111, J112, J113, J114, J115, J116, J117, J118, J119, J12, J120, J121, J122, J123, J124, J125, J126, J127, J128, J129, J13, J130, J131, J132, J133, J134, J135, J136, J137, J138, J139, J14, J140, J141, J142, J143, J144, J145, J146, J147, J148, J149, J15, J150, J151, J152, J153, J154, J155, J156, J157, J158, J159, J16, J160, J161, J162, J17, J18, J19, J2, J20, J21, J22, J23, J24, J25, J26, J27, J28, J29, J3, J30, J31, J32, J33, J34, J35, J36, J37, J38, J39, J4, J40, J41, J42, J43, J44, J45, J46, J47, J48, J49, J5, J50, J51, J52, J53, J54, J55, J56, J57, J58, J59, J6, J60, J61, J62, J63, J64, J65, J66, J67, J68, J69, J7, J70, J71, J72, J73, J74, J75, J76, J77, J78, J79, J8, J80, J83, J84, J85, J86, J87, J88, J89, J9, J90, J91, J92, J93, J94, J95, J96, J97, J98, J99",TestPoint_Pad_1.5x1.5mm,160,Conn_01x01_Pin,
J81,USB_C_Receptacle_HCTL_HC-TYPE-C-16P-01A,1,USB_C_Receptacle_USB2.0_16P,
J82,PinHeader_1x05_P2.54mm_Vertical,1,Conn_01x05,
"LED1, LED10, LED11, LED12, LED13, LED14, LED15, LED16, LED2, LED3, LED4, LED5, LED6, LED7, LED8, LED9",LED_1088_Pin_Header,16,1088AS,
"R1, R10, R11, R12, R13, R14, R15, R16, R2, R3, R4, R5, R6, R7, R8, R9",0805,16,68k,
R17,0805,1,1k,
"R18, R19, R24, R25, R26",0805,5,10k,
"R20, R21",0805,2,5.1k,
"R22, R23",0805,2,4k7,
R27,0805,1,10,
SW1,SW_PUSH_6mm_H5mm,1,Boot,
SW2,SW_PUSH_6mm_H5mm,1,Factory Reset,
SW3,SW_PUSH_6mm_H5mm,1,Reset,
"U1, U10, U11, U12, U13, U14, U15, U16, U2, U3, U4, U5, U6, U7, U8, U9",SOIC-24W_7.5x15.4mm_P1.27mm,16,MAX7219CWG,
U17,SOT-223-3_TabPin2,1,TLV76133DCY,
U18,ESP32-S3-WROOM-1,1,ESP32-S3-WROOM-1,
U19,TSSOP-20_4.4x6.5mm_P0.65mm,1,74HCT245,
U20,SOIC-16W_7.5x10.3mm_P1.27mm,1,DS3231S,
U21,XDCR_VEML7700-TT,1,VEML7700-TT,

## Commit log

2026-04-09 Initial release v1.4.7
2026-04-28 fix: Review-Punkte einarbeiten
2026-04-28 OTA Repair
2026-04-28 fix: cspell und platformio stabilisieren
2026-04-28 chore: ignoriere lokale Node-Abhaengigkeiten
2026-04-28 build: setze OTA als PlatformIO-Default
2026-04-29 refactor: NtpLogEntry von String auf char[]-Buffer umgestellt
    - NtpLogEntry.host und .detail sind jetzt char[NTP_LOG_HOST_LEN] bzw.
    char[NTP_LOG_DETAIL_LEN] statt String – vermeidet Heap-Fragmentierung
    im NTP-Log-Ringpuffer.
    - ntpLogAdd() verwendet strlcpy() statt direkter String-Zuweisung.
    - cspell.json: ntplog ergänzt.
    Ref: review-2026-04-29-ntplog-char
2026-04-29 docs: Changelog-Referenzen auf Commit ea26b7a korrigiert
2026-05-10 feat: portiere Firmware auf ESP32-S3-Platine
2026-05-10 fix: setze Reset- und I2C-Pins auf Platinenbelegung
2026-05-10 fix: stabilisiere S3-USB-Uploadpfad
2026-05-10 fix: initialisiere LittleFS auf dem ESP32-S3
2026-05-10 fix: nutze eigenen SPI-Bus fuer das Display
2026-05-10 fix: nutze HSPI fuer das Display
2026-05-10 fix: nutze direkten GPIO-Modus fuer das Display
2026-05-10 fix: drehe obere module und synchronisiere ntp sofort
2026-05-10 fix: korrigiere reihenfolge der oberen module
2026-05-10 fix: integriere VEML7700 autohelligkeit
2026-05-10 fix: zeige i2c-diagnose fuer veml7700 an
2026-05-10 fix: entkopple webserver und fuege ota-task hinzu
2026-05-10 fix: wiederhole veml7700-init bei nack
2026-05-10 fix: ota auch im ap-modus aktivieren
2026-05-10 fix: i2c-diagnose um ds3231 erweitern
2026-05-11 fix: pwm-dimmen loopbasiert machen
2026-05-11 fix: ntp-bei-start schneller erneut versuchen
2026-05-11 fix: ntp-retry an dns-status binden
2026-05-11 feat: ds3231 als zeitquelle integrieren
2026-05-11 feat: rtc-tab und manuelle zeiteinstellung ergänzen
2026-05-11 feat: rtc als laufzeitquelle und rtc-status ergänzen
2026-05-11 docs: markdownlint im changelog abschalten
2026-05-11 docs: readme um rtc- und sensordetails erweitern
2026-05-11 docs: cr2032-pufferung der rtc dokumentieren
2026-05-11 docs: kicad-projektspiegel ins repo uebernehmen
2026-05-11 feat: firmware-installer und release 1.5.0
2026-05-11 docs: firmware-installer im README verlinken
2026-05-11 docs: web-updater-link im README ergaenzen
2026-05-11 docs: mDNS-link als lokales netz kennzeichnen
2026-05-11 feat: browser-installer als codeberg pages bereitstellen
2026-05-11 docs: projektbild und pages-link nachziehen
2026-05-11 docs: installer-badge in der README ergaenzen
2026-05-11 feat: dark mode fuer die Web-UI
2026-05-11 fix: uhranzeige im webui dunkel lassen
2026-05-15 fix: Webserver-Header umbenannt wegen Namenskonflikt unter Windows
    src/webserver.h in src/ClockWebUi.h umbenannt, um Konflikte mit dem
    ESP32-Framework-Header <WebServer.h> auf case-insensitiven Dateisystemen
    zu vermeiden. Includes, README, cspell und Changelog nachgezogen.
2026-05-15 docs: commit-hash im changelog-eintrag korrigiert
2026-05-15 docs: changelog-regel auf commit-id-pflicht verschaerft
2026-05-15 fix: ntp-subsekunden-praezision und halbe round-trip-zeit auswerten
    Subsekunden-Anteil der NTP-Transmit-Timestamp und halbe Round-Trip-Zeit
    werden jetzt ausgewertet und auf die naechste ganze Sekunde gerundet,
    bevor die RTC gesetzt wird. Behebt den ~1-Sekunden-Nachlauf der Uhrzeit.
2026-05-15 docs: commit-id im changelog fuer ntp-fix korrigiert
2026-05-15 fix: scroll-effekt mit gettimeofday-kompensation repariert
    Die fehlerhafte gettimeofday()-basierte Subsekunden-Kompensation
    in drawTimeHHMMSS() entfernt. gettimeofday() lieferte auf dem ESP32
    uninitialisierte Werte, wodurch die Animation auf einen Frame
    verkuerzt wurde und der Scroll-Effekt unsichtbar blieb.
2026-05-15 docs: commit-id im changelog fuer scroll-fix korrigiert
2026-05-15 fix: ntp-subsekunden-genauigkeit durch sekundengrenz-sync verbessert
    Vor dem RTC-Schreiben wird jetzt gezielt auf die naechste volle
    Sekundengrenze gewartet, damit die RTC exakt zur Sekundenmitte
    loslaeuft. Eliminiert den variablen Subsekunden-Versatz zwischen
    mehreren unabhaengig synchronisierten Uhren.
2026-05-15 docs: commit-id im changelog fuer sekundengrenz-fix korrigiert
2026-05-15 feat: helligkeitsregler dual genutzt - absolut bei VEML7700 aus, relativ bei VEML7700 ein
2026-05-15 docs: commit-id im changelog fuer dualen helligkeitsregler korrigiert
2026-05-15 fix: race-condition beim speichern entfernt - brightness-update aus web-task entfernt
2026-05-15 docs: commit-id im changelog fuer race-condition-fix korrigiert
2026-05-15 fix: compiler-caching und race-condition behoben - cfg-werte werden nicht mehr gecached, scroll-state-reset ueber flag
2026-05-15 docs: commit-id im changelog fuer compiler-caching-fix korrigiert
2026-05-15 chore: AGENTS.md aus versionierung entfernt
2026-05-15 perf: WiFi.RSSI()-Aufrufe vorgezogen um Blockade beim HTML-Streaming zu vermeiden
2026-05-16 build: cspell als lokale devDependency ergänzt, .kilo/ in .gitignore
2026-06-04 fix: korrigierte Platine V0.5
